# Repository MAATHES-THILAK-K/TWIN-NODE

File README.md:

## 📌 Project Overview

**TWIN-NODE** is a **two-node, ultra-low-power water level monitoring system** for overhead tanks.
It uses **ESP-NOW wireless communication**, requires **no internet**, and is optimized for **solar-powered outdoor operation**.

This project is **designed for manufacturable PCBs**, with all components chosen for reliability and low power.

---

## 🧩 System Architecture

| Node                             | Description                                                                             |
| -------------------------------- | --------------------------------------------------------------------------------------- |
| **NODE-1 (Outdoor Sensor Node)** | Measures water level using a waterproof ultrasonic sensor and transmits data wirelessly |
| **NODE-2 (Indoor Display Node)** | Receives water level data and alerts the user using LEDs and a buzzer                   |

---

## 🔧 NODE-1 – Outdoor Sensor Node

| Feature       | Description                               |
| ------------- | ----------------------------------------- |
| Controller    | ESP-12F (ESP8266)                              |
| Sensor        | SR04M / JSN-SR04T Waterproof Ultrasonic /HCSRO4|
| Power Source  | 18650 Li-ion Battery                      |
| Charging      | Solar Panel + TP4056                      |
| Regulation    | RT9080-3.3 V LDO                          |
| Communication | ESP-NOW                                   |
| Power Saving  | Deep Sleep + GPIO-controlled sensor power |
| Installation  | Weatherproof Enclosure                    |

---

## 🔋 Low-Power Design

| Technique                      | Purpose                           |
| ------------------------------ | --------------------------------- |
| Deep Sleep Mode                | Minimizes battery consumption     |
| GPIO-controlled Sensor Power   | Cuts sensor standby current       |
| LDO with low quiescent current | Efficient voltage regulation      |
| ESP-NOW                        | Low-energy wireless communication |

---

## 📂 Repository Structure

| Folder            | Purpose                                                |
| ----------------- | ------------------------------------------------------ |
| `TWIN NODE V1.0/` | Stable, tested hardware revision                       |
| `TWIN NODE V2.0/` | Updated hardware revision (new features, improvements) |
| `Gerber/`         | Manufacturing-ready files                              |
| `IMAGES/`         | PCB renders and photos                                 |
| `REPORT/`         | ERC, DRC, design checks                                |
| `3D MODELS/`      | Mechanical references                                  |
| `LICENSE`         | Open-source licensing information                      |
| `README.md`       | Project overview and documentation                     |

---

## 🚀 Engineering Note

* Designed for **low-power operation**
* **Solar and battery-friendly**
* **Manufacturable PCB**
* Versioned structure makes it easy to track revisions

---

### 👤 Author

**MAATHES-THILAK-K (KMT)**
Embedded Systems | PCB Design | Robotics

---

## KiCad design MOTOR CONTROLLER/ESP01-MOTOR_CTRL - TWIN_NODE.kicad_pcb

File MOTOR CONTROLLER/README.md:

# ⚙️ TWIN-NODE – Motor Controller
## Overview

The **TWIN-NODE Motor Controller** is a compact wireless motor control module designed to work with the TWIN-NODE water level monitoring system.
It enables **remote ON/OFF control of a water pump** using **ESP-NOW**, without internet connectivity.

---

---

## Key Features

* ESP-01 (ESP8266) based controller
* Wireless control using ESP-NOW
* Relay-based motor switching
* Electrical isolation between control and load
* Manufacturable PCB design

---

## Hardware Summary

| Item          | Description        |
| ------------- | ------------------ |
| MCU           | ESP-01 (ESP8266)   |
| Communication | ESP-NOW            |
| Motor Control | Relay   |
| PCB Files     | KiCad + Gerber     |
| Application   | Water pump control |

---

## Repository Contents

* Gerber files for manufacturing
* KiCad schematic & PCB
* 3D models and images
* Design reports (ERC/DRC)

---

## Author

**MAATHES-THILAK-K (KMT)**
Embedded Systems | PCB Design | Robotics

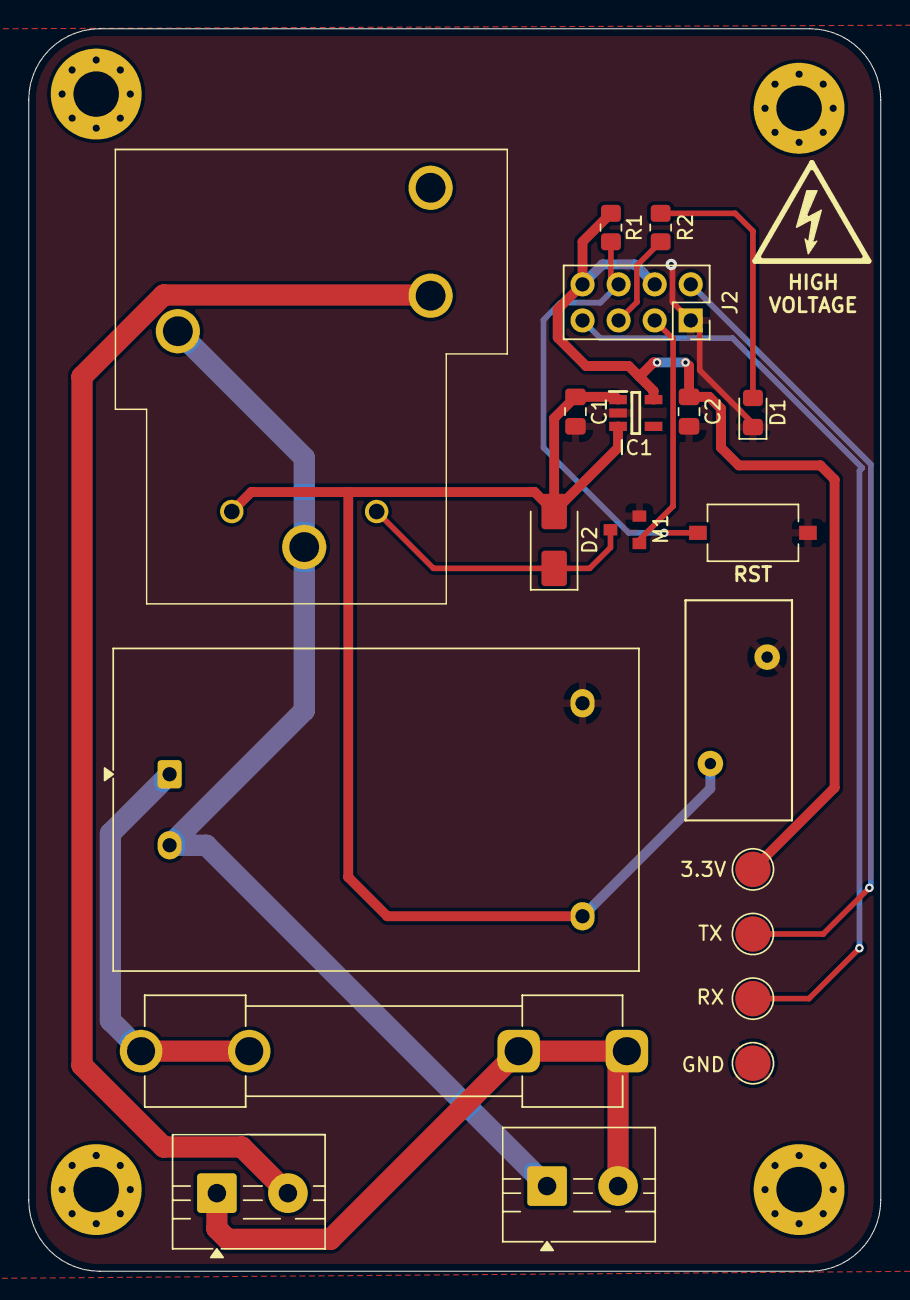
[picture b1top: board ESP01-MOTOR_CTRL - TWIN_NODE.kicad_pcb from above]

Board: 2 copper layers, 60.0 x 87.5 mm, 24 parts (0 on the bottom side), 14 nets.

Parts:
3.3V: TestPoint; TestPoint_Pad_D2.5mm
C1, C2: 10uF; C_0805_2012Metric_Pad1.18x1.45mm_HandSolder
D1: LED; LED_0805_2012Metric_Pad1.15x1.40mm_HandSolder
D2: SS12; D_SMA
F1: 250V@500mA; Fuseholder_Clip-6.3x32mm_Littelfuse_102_122_Inline_P34.21x7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
GND: TestPoint; TestPoint_Pad_D2.5mm
H1, H2, H3, H4: MH; MountingHole_3.2mm_M3_Pad_Via
IC1: RT9080-33GJ5; SOT94P280X100-5N
J1: MOTOR; TerminalBlock_MaiXu_MX126-5.0-02P_1x02_P5.00mm
J2: 02X04; PinSocket_2x04_P2.54mm_Vertical
J3: INPUT; TerminalBlock_MaiXu_MX126-5.0-02P_1x02_P5.00mm
K1: SLA-5VDC-SL-C; RELAY_SLA-12VDC-SL-C
M1: SI2300; SOT-23
PS1: HLK-PM01; Converter_ACDC_Hi-Link_HLK-PMxx
R1: 10K; R_0805_2012Metric_Pad1.20x1.40mm_HandSolder
R2: 1K; R_0805_2012Metric_Pad1.20x1.40mm_HandSolder
RV1: 275V-14D; RV_Disc_D15.5mm_W7.5mm_P7.5mm
RX: TestPoint; TestPoint_Pad_D2.5mm
SW1: SW_Push; SW_Tactile_SPST_NO_Straight_CK_PTS636Sx25SMTRLFS
TX: TestPoint; TestPoint_Pad_D2.5mm

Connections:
/3.3V: 3.3V.1, C2.1, IC1.5 (VOUT), J2.4, J2.8, R1.1
/5V: C1.1, D2.2 (A), IC1.1 (VIN), IC1.3 (EN), K1.C1, PS1.4 (+Vout), RV1.1
/RST: J2.6, R1.2, SW1.1
FUSED_LIVE: F1.2, PS1.1 (AC/L)
GND: C1.2, C2.2, D1.1 (K), GND.1, IC1.2 (GND), J2.1, M1.2, PS1.3 (-Vout), RV1.2, SW1.2
GPIO0: J2.5, R2.1
GPIO2: J2.3, M1.1
LIVE: F1.1, J1.1, J3.2
NEUTRAL: J3.1, K1.COM1, K1.COM2, PS1.2 (AC/N)
NEUTRAL_BREAK: J1.2, K1.NO
unnamed: D1.2 (A), R2.2
unnamed: D2.1 (K), K1.C2, M1.3
RX: J2.7, RX.1
TX: J2.2, TX.1

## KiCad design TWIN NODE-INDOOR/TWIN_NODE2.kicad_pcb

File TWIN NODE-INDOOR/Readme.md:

# TWIN-NODE – Indoor Node

## Overview

The **Indoor Node** is a **battery-powered, ultra-low-power receiver and alert unit** for the TWIN-NODE water level monitoring system.
It receives water level data from the outdoor sensor node using **ESP-NOW** and provides **local LED and buzzer alerts**, without internet or Wi-Fi infrastructure.

---

## Key Features

* ESP-NOW wireless communication
* Battery-powered operation
* Ultra-low-power design
* LED level indication
* Buzzer alert for critical levels
* No internet, no router, no cloud

---

## Hardware Summary

| Item          | Specification     |
| ------------- | ----------------- |
| MCU           | ESP-12F (ESP8266) |
| Communication | ESP-NOW           |
| Indicators    | LEDs              |
| Alert         | Buzzer            |
| Power Source  | Battery           |
| Design Tool   | KiCad             |

---

## Power Design

* Deep sleep enabled
* Wake on ESP-NOW receive
* Minimal standby current
* Optimized for long-term battery life

---

## Repository Contents

| Path                 | Description         |
| -------------------- | ------------------- |
| `GERBER/`            | Manufacturing files |
| `IMAGES/`            | PCB images          |
| `REPORT/`            | ERC / DRC           |
| `3D MODELS/`         | Mechanical models   |
| `TWIN_NODE2.kicad_*` | Schematic & PCB     |

---

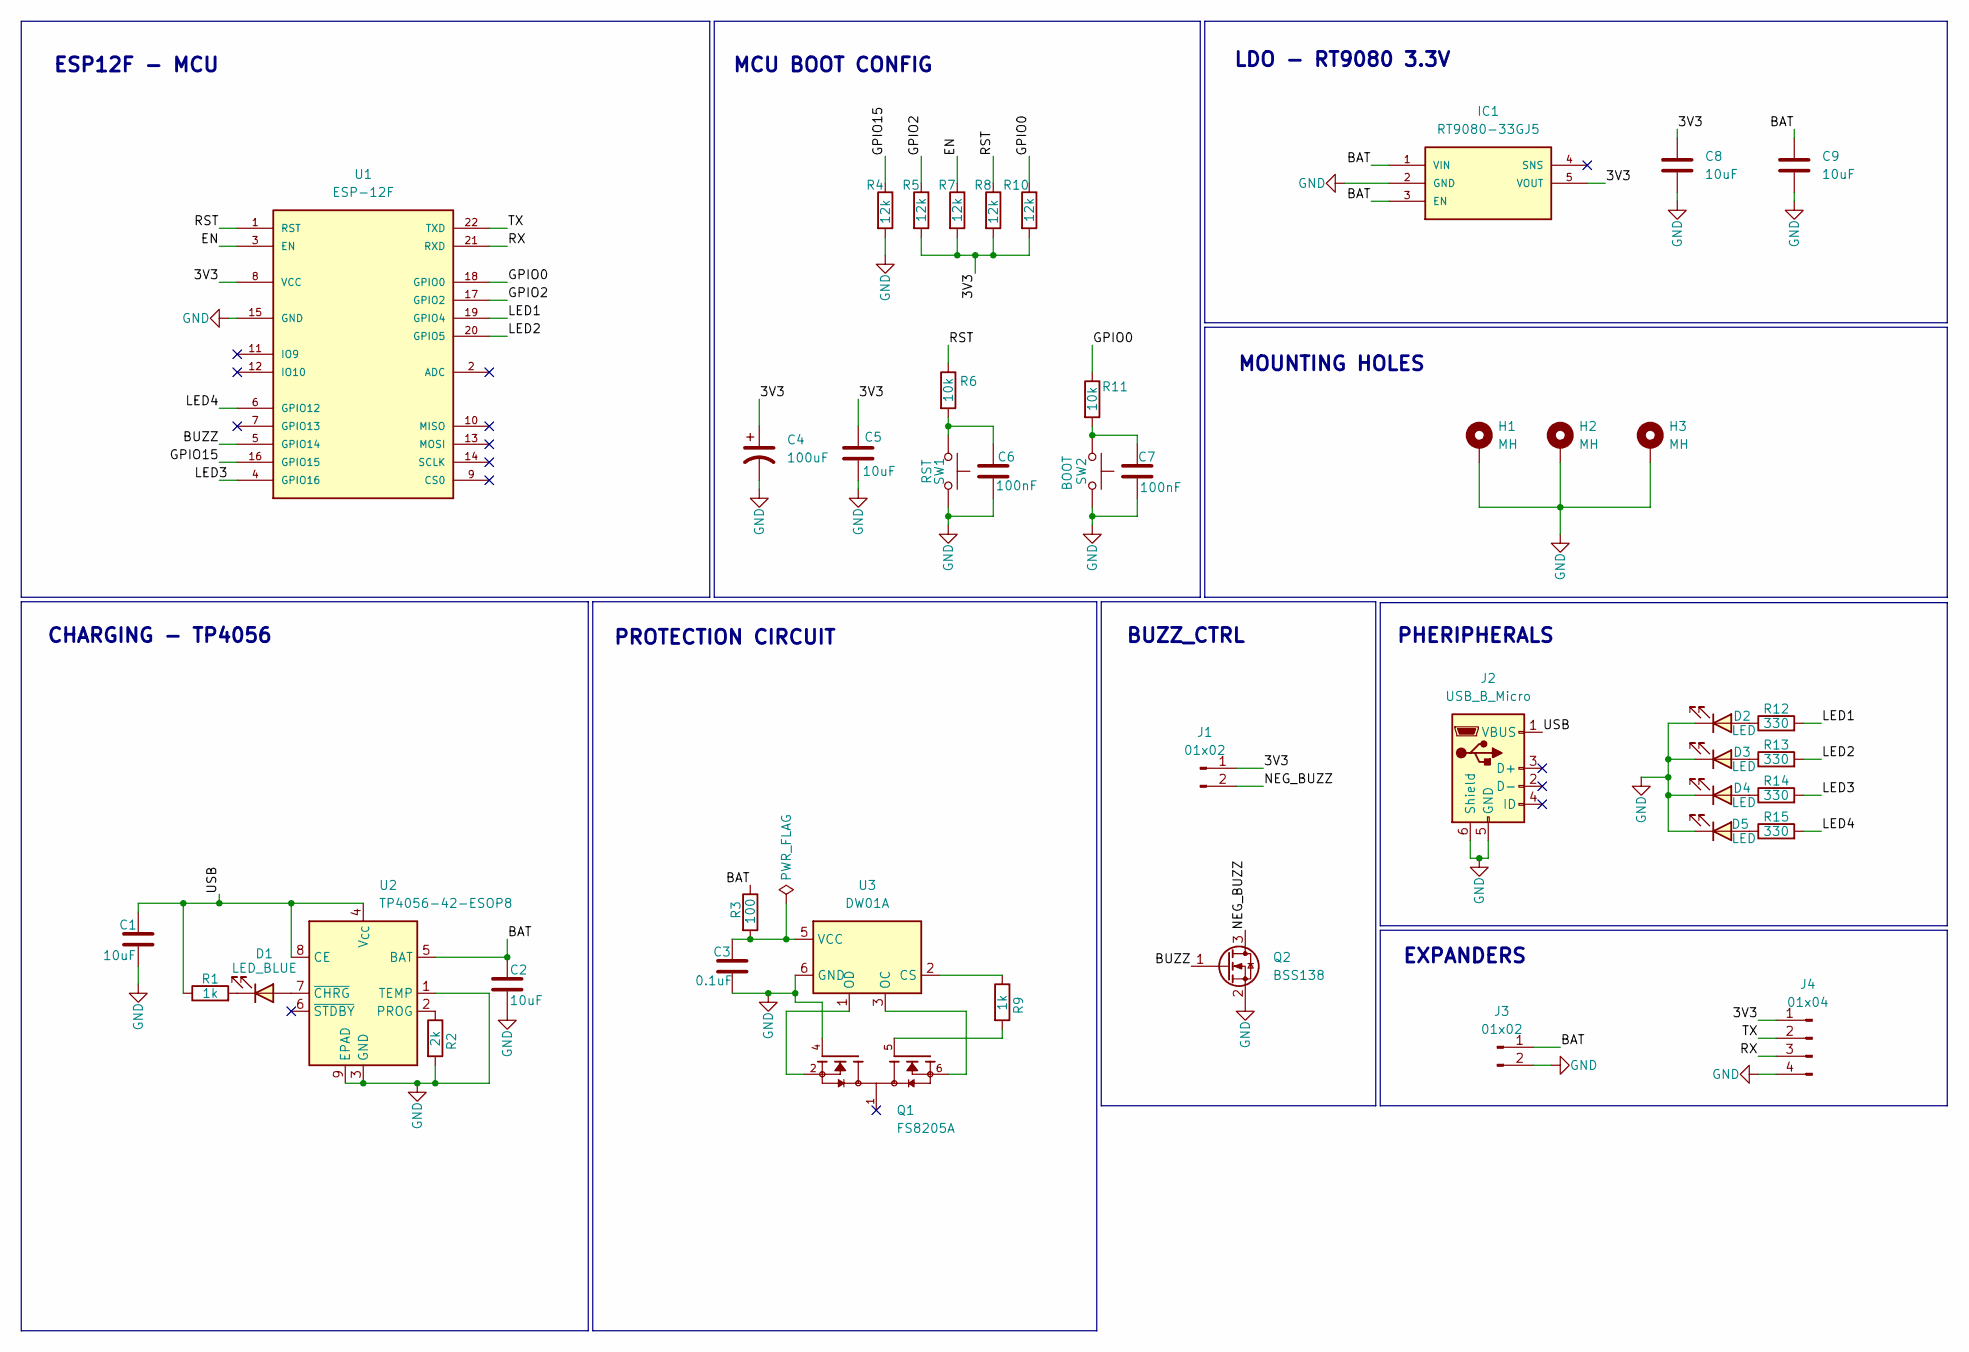
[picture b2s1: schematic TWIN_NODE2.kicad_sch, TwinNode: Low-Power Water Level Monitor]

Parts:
C1, C2, C5, C8, C9: 10uF; C_0805_2012Metric_Pad1.18x1.45mm_HandSolder
C3: 0.1uF; C_0805_2012Metric_Pad1.18x1.45mm_HandSolder
C4: 100uF; CP_Elec_5x5.3
C6, C7: 100nF; C_0805_2012Metric_Pad1.18x1.45mm_HandSolder
D1: LED_BLUE; SolderWire-0.1sqmm_1x02_P3.6mm_D0.4mm_OD1mm
D2, D3, D4, D5: LED; SolderWire-0.1sqmm_1x02_P3.6mm_D0.4mm_OD1mm
H1, H2, H3: MH; MountingHole_3.2mm_M3_Pad_Via
IC1: RT9080-33GJ5; SOT94P280X100-5N
J1: 01x02; SolderWire-0.1sqmm_1x02_P3.6mm_D0.4mm_OD1mm
J2: USB_B_Micro; USB_Micro-B_Molex_47346-0001
J3: 01x02; JST_SH_SM02B-SRSS-TB_1x02-1MP_P1.00mm_Horizontal
J4: 01x04; JST_SH_SM04B-SRSS-TB_1x04-1MP_P1.00mm_Horizontal
Q1: FS8205A; SOP65P640X120-8N; PARTREV 1.7
Q2: BSS138; SOT-23
R1, R9: 1k; R_0805_2012Metric_Pad1.20x1.40mm_HandSolder
R2: 2k; R_0805_2012Metric_Pad1.20x1.40mm_HandSolder
R3: 100; R_0805_2012Metric_Pad1.20x1.40mm_HandSolder
R4, R5, R7, R8, R10: 12k; R_0805_2012Metric_Pad1.20x1.40mm_HandSolder
R6, R11: 10k; R_0805_2012Metric_Pad1.20x1.40mm_HandSolder
R12, R13, R14, R15: 330; R_0805_2012Metric_Pad1.20x1.40mm_HandSolder
SW1: RST; SW_Tactile_SPST_NO_Straight_CK_PTS636Sx25SMTRLFS
SW2: BOOT; SW_Tactile_SPST_NO_Straight_CK_PTS636Sx25SMTRLFS
U1: ESP-12F
U2: TP4056-42-ESOP8; SOIC-8-1EP_3.9x4.9mm_P1.27mm_EP2.41x3.3mm_ThermalVias
U3: DW01A; SOT-23-6

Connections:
/3V3: C4.1, C5.1, C8.1, IC1.5 (VOUT), J1.1, J4.1, R5.2, R7.2, R8.2, R10.2, U1.8 (VCC)
/BAT: C2.1, C9.1, IC1.1 (VIN), IC1.3 (EN), J3.1, R3.1, U2.5 (BAT)
/BUZZ: Q2.1 (G), U1.5 (GPIO14)
/EN: R7.1, U1.3 (EN)
/GPIO0: R10.1, R11.1, U1.18 (GPIO0)
/GPIO2: R5.1, U1.17 (GPIO2)
/GPIO15: R4.1, U1.16 (GPIO15)
/LED1: R12.2, U1.19 (GPIO4)
/LED2: R13.2, U1.20 (GPIO5)
/LED3: R14.2, U1.4 (GPIO16)
/LED4: R15.2, U1.6 (GPIO12)
/NEG_BUZZ: J1.2, Q2.3 (D)
/RST: R6.1, R8.1, U1.1 (RST)
/RX: J4.3, U1.21 (RXD)
/TX: J4.2, U1.22 (TXD)
/USB: C1.1, J2.1 (VBUS), R1.1, U2.4 (V_{CC}), U2.8 (CE)
GND: C1.2, C2.2, C3.2, C4.2, C5.2, C6.2, C7.2, C8.2, C9.2, D2.1 (K), D3.1 (K), D4.1 (K), D5.1 (K), H1.1, H2.1, H3.1, IC1.2 (GND), J2.5 (GND), J2.6 (Shield), J3.2, J4.4, Q1.4, Q2.2 (S), R2.2, R4.2, SW1.2, SW2.2, U1.15 (GND), U2.1 (TEMP), U2.3 (GND), U2.9 (EPAD), U3.6 (GND)
unnamed: C6.1, R6.2, SW1.1
unnamed: C7.1, R11.2, SW2.1
unnamed: D1.2 (A), U2.7 (~CHRG)
unnamed: D1.1 (K), R1.2
unnamed: D2.2 (A), R12.1
unnamed: D3.2 (A), R13.1
unnamed: D4.2 (A), R14.1
unnamed: D5.2 (A), R15.1
unnamed: Q1.5, R9.2
unnamed: R2.1, U2.2 (PROG)
unnamed: R9.1, U3.2 (CS)
unnamed: Q1.6, Q1.7, U3.3 (OC)
unnamed: Q1.2, Q1.3, U3.1 (OD)
unnamed: C3.1, R3.2, U3.5 (VCC)

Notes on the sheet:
MCU BOOT CONFIG
CHARGING - TP4056
EXPANDERS
ESP12F - MCU
LDO - RT9080 3.3V
PROTECTION CIRCUIT
BUZZ_CTRL
MOUNTING HOLES
PHERIPHERALS

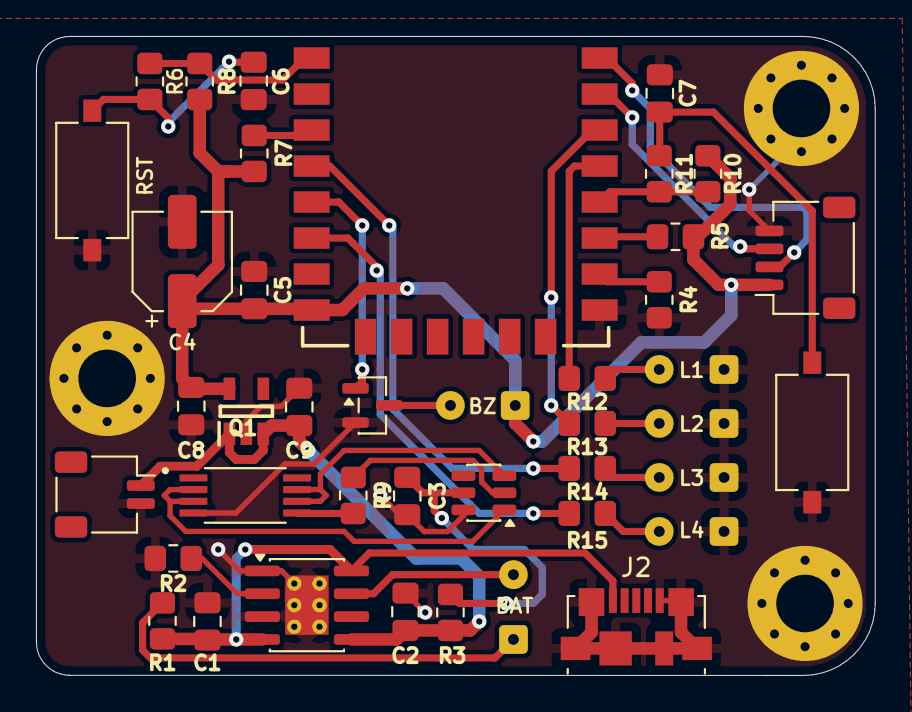
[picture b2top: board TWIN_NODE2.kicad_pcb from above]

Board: 2 copper layers, 46.6 x 35.5 mm, 44 parts (0 on the bottom side), 31 nets.

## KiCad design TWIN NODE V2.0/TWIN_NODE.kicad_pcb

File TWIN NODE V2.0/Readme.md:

# TWIN NODE V2.0

### Low-Power Outdoor Water Level Sensor Node – Improved Design

---

## 📌 Overview

**TWIN NODE V2.0** is the **fabricated and tested hardware revision** of the low-power ESP-NOW water level monitoring system.
This version incorporates **real-world fabrication feedback**, improving reliability and simplifying the design for future revisions.

All components are sourced from [ROBU.IN](https://robu.in).

---

## ⚙️ Key Updates from V1.0

* **Mounting holes:** Increased from 3 to **4** for better casing support
* **I2C expanders:** Removed, no longer required
* **Programming & power connections:** Female headers replaced with **JST connectors**
* **Component placement:** Fully optimized for **aesthetic and practical routing**
* **PCB traces:** Increased width to support **longer interconnections**
* **PCB size:** ~45 × 45 mm
* **DRC & ERC:** Fully verified
* **Fabricated & powered ON successfully**

---

## 🛠️ Fabrication Feedback & Design Correction (Important)

During physical testing of the fabricated PCB, the following observation was made:

### ❌ Unnecessary Pull-Up Resistors Identified

* **GPIO0 (BOOT)** – 10 kΩ resistor **not required**
* **RST (RESET)** – 10 kΩ resistor **not required**

These resistors were found to be **redundant** and **can be safely removed** in future PCB revisions.

### ✅ Reason

* ESP8266 12K pull-ups are sufficient for:

  * Normal boot operation
  * Reliable reset behavior
* External 10 kΩ resistors on **GPIO0** and **RST**:

  * Do **not improve stability**
  * Increase component count unnecessarily
  * Slightly complicate routing and assembly

➡️ **Action for next revision:**
Remove the 10 kΩ pull-up resistors on **GPIO0 (BOOT)** and **RST**.

---

## 🔧 Design Notes

* Designed for **battery + solar operation**
* Optimized for **low power outdoor deployment**
* ESP-NOW based communication (no Wi-Fi AP dependency)
* Layout finalized with **manufacturability in mind**
* Suitable for **field deployment and enclosure mounting**

---

## 📦 Project Status

✔ PCB fabricated
✔ Power-up verified
✔ Boot & reset behavior validated
✔ Design improvement identified for next revision

---

### 👤 Author

**MAATHES-THILAK-K (KMT)**
Embedded Systems | PCB Design | Robotics

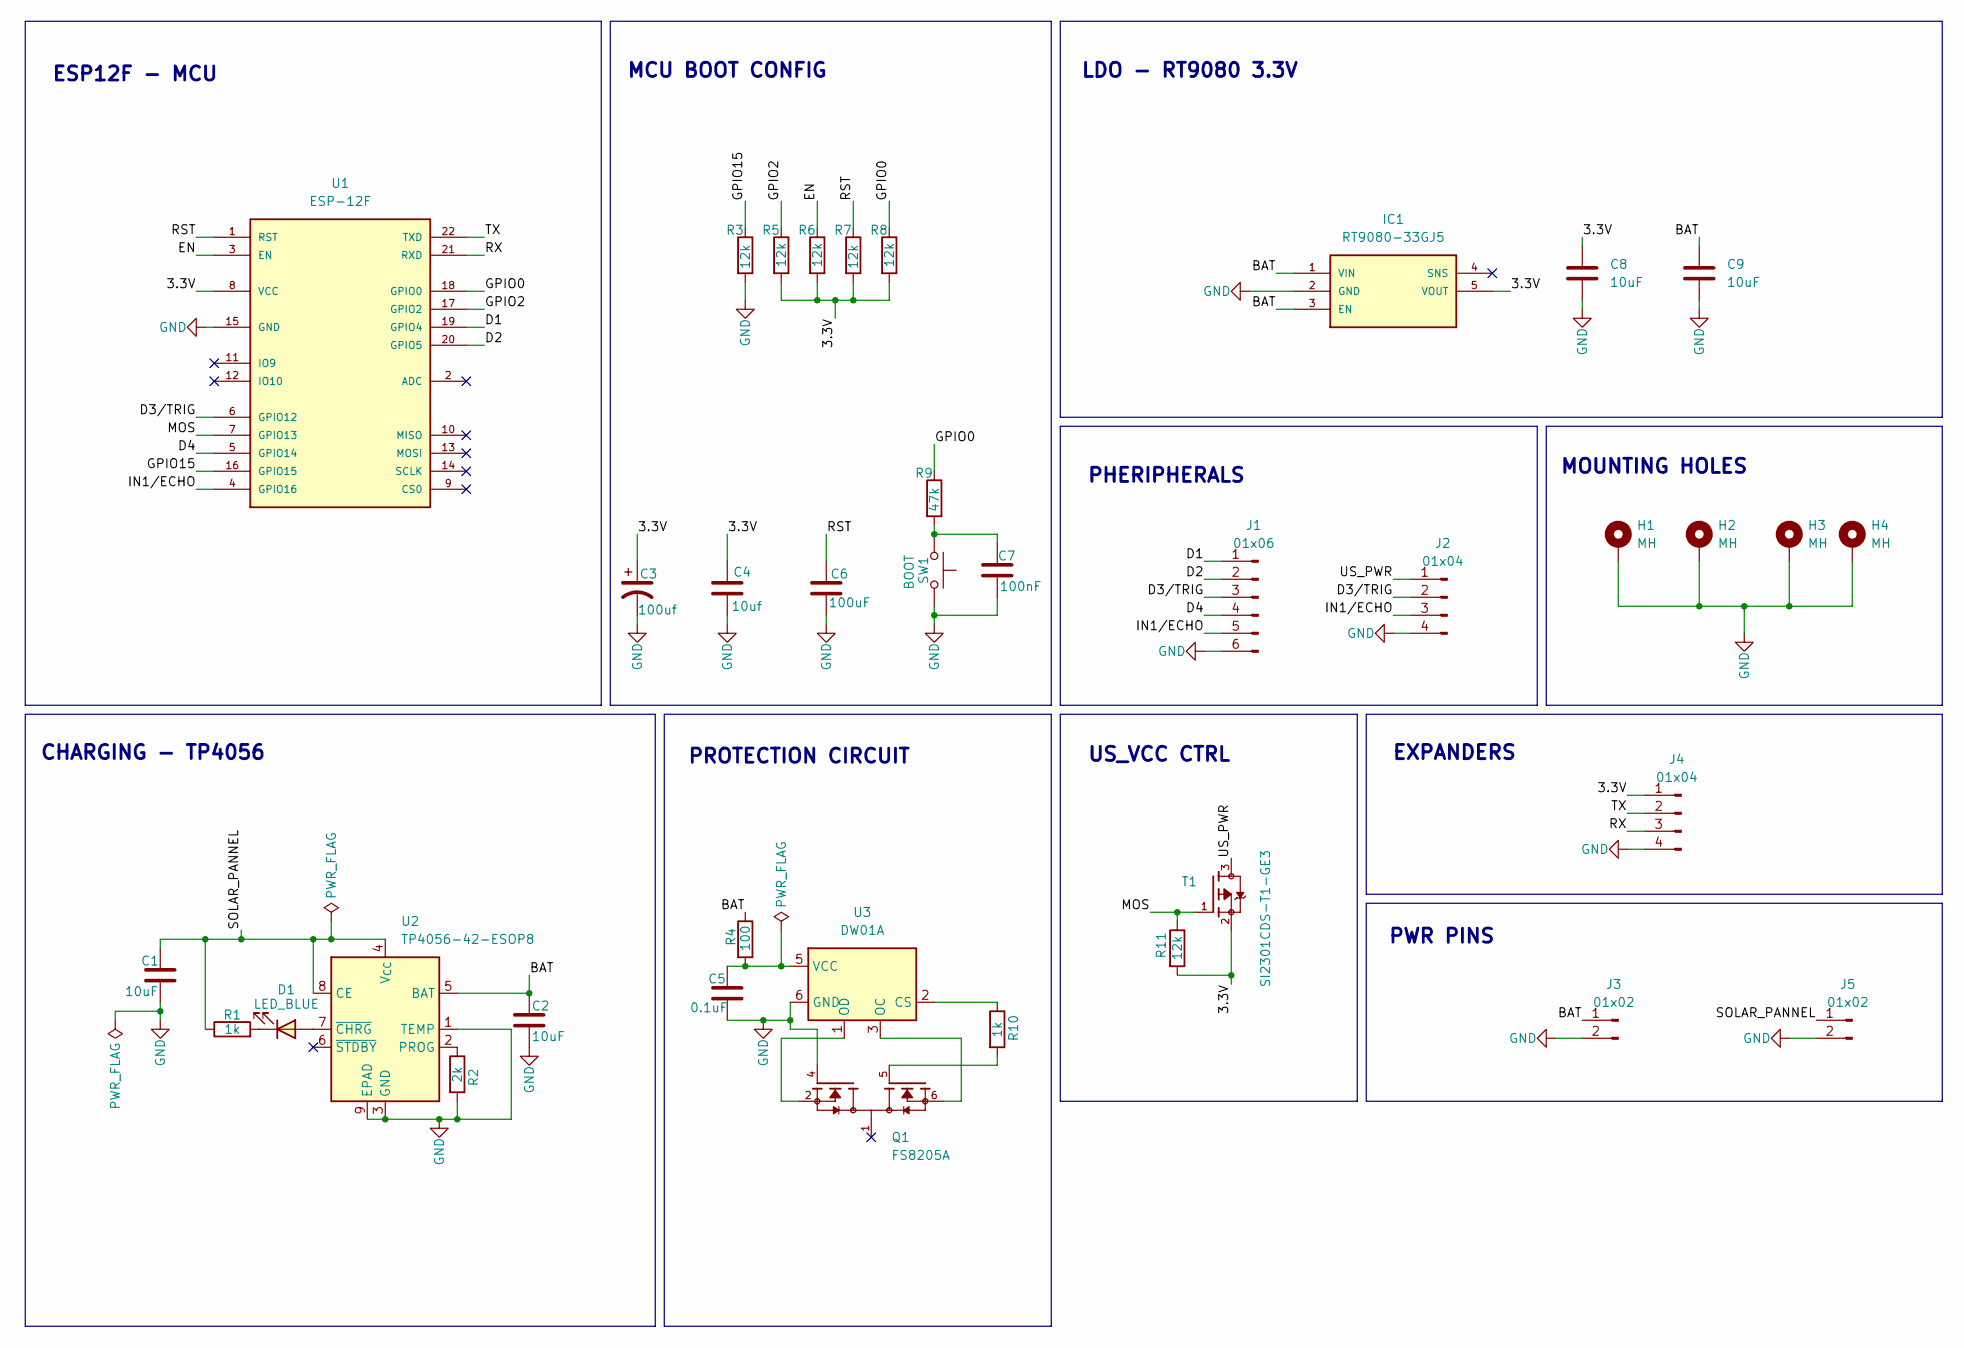
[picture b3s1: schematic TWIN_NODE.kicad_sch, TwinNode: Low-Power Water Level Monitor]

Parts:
C1, C2, C8, C9: 10uF; C_0805_2012Metric_Pad1.18x1.45mm_HandSolder
C3: 100uf; CP_Elec_8x10.5
C4: 10uf; C_0805_2012Metric_Pad1.18x1.45mm_HandSolder
C5: 0.1uF; C_0805_2012Metric_Pad1.18x1.45mm_HandSolder
C6: 100uF; C_0805_2012Metric_Pad1.18x1.45mm_HandSolder
C7: 100nF; C_0805_2012Metric_Pad1.18x1.45mm_HandSolder
D1: LED_BLUE; LED_0805_2012Metric_Pad1.15x1.40mm_HandSolder
H1, H2, H3, H4: MH; MountingHole_3.2mm_M3_Pad_Via
IC1: RT9080-33GJ5; SOT94P280X100-5N
J1: 01x06; JST_SH_SM06B-SRSS-TB_1x06-1MP_P1.00mm_Horizontal
J2, J4: 01x04; JST_SH_SM04B-SRSS-TB_1x04-1MP_P1.00mm_Horizontal
J3, J5: 01x02; JST_SH_SM02B-SRSS-TB_1x02-1MP_P1.00mm_Horizontal
Q1: FS8205A; SOP65P640X120-8N; PARTREV 1.7
R1, R10: 1k; R_0805_2012Metric_Pad1.20x1.40mm_HandSolder
R2: 2k; R_0805_2012Metric_Pad1.20x1.40mm_HandSolder
R3, R5, R6, R7, R8, R11: 12k; R_0805_2012Metric_Pad1.20x1.40mm_HandSolder
R4: 100; R_0805_2012Metric_Pad1.20x1.40mm_HandSolder
R9: 47k; R_0805_2012Metric_Pad1.20x1.40mm_HandSolder
SW1: BOOT; SW_Tactile_SPST_NO_Straight_CK_PTS636Sx25SMTRLFS
T1: SI2301CDS-T1-GE3; SOT-23
U1: ESP-12F
U2: TP4056-42-ESOP8; SOIC-8-1EP_3.9x4.9mm_P1.27mm_EP2.41x3.3mm_ThermalVias
U3: DW01A; SOT-23-6

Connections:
/3.3V: C3.1, C4.1, C8.1, IC1.5 (VOUT), J4.1, R5.2, R6.2, R7.2, R8.2, R11.2, T1.2, U1.8 (VCC)
/BAT: C2.1, C9.1, IC1.1 (VIN), IC1.3 (EN), J3.1, R4.1, U2.5 (BAT)
/D1: J1.1, U1.19 (GPIO4)
/D2: J1.2, U1.20 (GPIO5)
/D3/TRIG: J1.3, J2.2, U1.6 (GPIO12)
/D4: J1.4, U1.5 (GPIO14)
/EN: R6.1, U1.3 (EN)
/GPIO0: R8.1, R9.1, U1.18 (GPIO0)
/GPIO2: R5.1, U1.17 (GPIO2)
/GPIO15: R3.1, U1.16 (GPIO15)
/IN1/ECHO: J1.5, J2.3, U1.4 (GPIO16)
/MOS: R11.1, T1.1, U1.7 (GPIO13)
/RST: C6.1, R7.1, U1.1 (RST)
/RX: J4.3, U1.21 (RXD)
/SOLAR_PANNEL: C1.1, J5.1, R1.1, U2.4 (V_{CC}), U2.8 (CE)
/TX: J4.2, U1.22 (TXD)
/US_PWR: J2.1, T1.3
GND: C1.2, C2.2, C3.2, C4.2, C5.2, C6.2, C7.2, C8.2, C9.2, H1.1, H2.1, H3.1, H4.1, IC1.2 (GND), J1.6, J2.4, J3.2, J4.4, J5.2, Q1.4, R2.2, R3.2, SW1.2, U1.15 (GND), U2.1 (TEMP), U2.3 (GND), U2.9 (EPAD), U3.6 (GND)
unnamed: C7.1, R9.2, SW1.1
unnamed: D1.2 (A), U2.7 (~CHRG)
unnamed: D1.1 (K), R1.2
unnamed: Q1.5, R10.2
unnamed: R2.1, U2.2 (PROG)
unnamed: R10.1, U3.2 (CS)
unnamed: Q1.6, Q1.7, U3.3 (OC)
unnamed: Q1.2, Q1.3, U3.1 (OD)
unnamed: C5.1, R4.2, U3.5 (VCC)

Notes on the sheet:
MCU BOOT CONFIG
LDO - RT9080 3.3V
US_VCC CTRL
ESP12F - MCU
PWR PINS
CHARGING - TP4056
PHERIPHERALS
EXPANDERS
MOUNTING HOLES
PROTECTION CIRCUIT

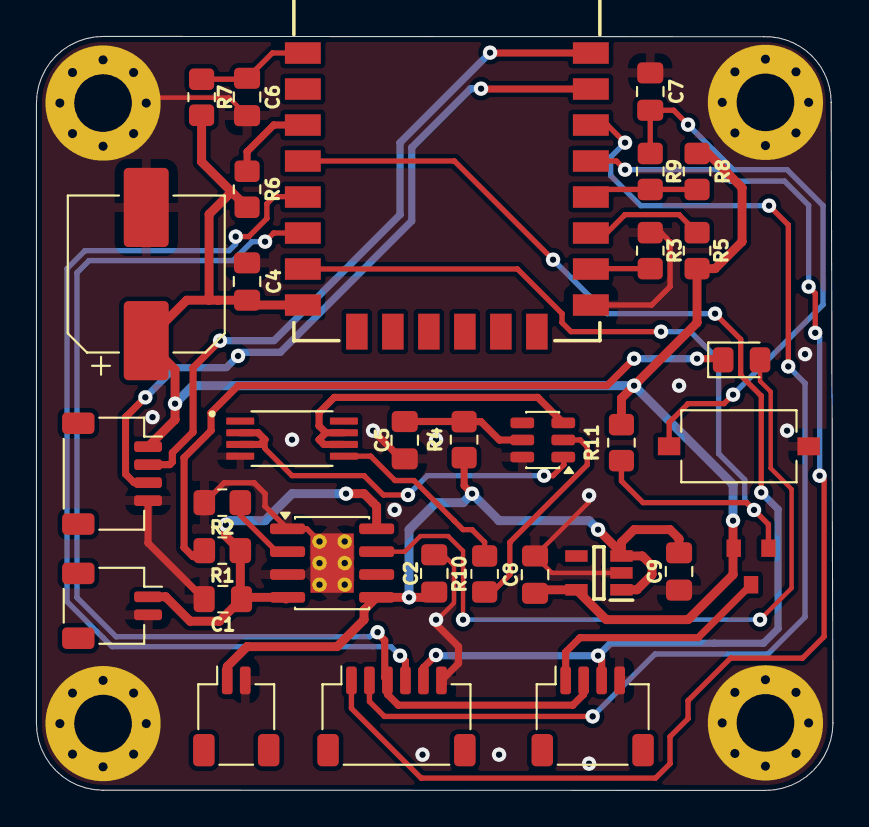
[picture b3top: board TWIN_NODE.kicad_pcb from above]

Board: 2 copper layers, 44.2 x 41.9 mm, 37 parts (0 on the bottom side), 27 nets.

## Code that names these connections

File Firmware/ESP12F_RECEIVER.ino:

#include <Arduino.h>
#include <ESP8266WiFi.h>
#include <espnow.h>

extern "C" {
  #include <user_interface.h>
}
//ESP12F MAC Address: 24:4C:AB:6C:E4:F8 - LION PCB TRANSMITTER
// --------------------------------------------------
// ESP32 TRANSMITTER MAC ADDRESS
// TX MAC Address: 24:6F:28:3A:B5:68
// --------------------------------------------------
uint8_t transmitterMacAddress[] = {0x24, 0x4C, 0xAB, 0x6C, 0xE4, 0xF8};

// --------------------------------------------------
// PIN CONFIGURATION - ESP12F RECEIVER
// --------------------------------------------------
#define LED_LOW_PIN     12   // GPIO12 - LOW level LED
#define LED_MED_PIN     16   // GPIO16 - MEDIUM level LED
#define LED_HIGH_PIN    5    // GPIO5  - HIGH level LED
#define LED_FULL_PIN    4    // GPIO4  - FULL level LED

#define BUZZER_PIN      14   // GPIO14 - Buzzer

// --------------------------------------------------
// ESP-NOW CHANNEL
// Must match transmitter channel
// --------------------------------------------------
#define ESPNOW_CHANNEL  1

// --------------------------------------------------
// DATA STRUCTURE
// Must match ESP32 transmitter structure
// --------------------------------------------------
typedef struct struct_message {
  float distanceCm;
  int waterPercent;
  int level;
  bool tankFull;
  bool tankEmpty;
} struct_message;

struct_message receivedData;

// --------------------------------------------------
// PRINT MAC ADDRESS
// --------------------------------------------------
void printMacAddress(uint8_t *mac) {
  for (int i = 0; i < 6; i++) {
    if (mac[i] < 16) Serial.print("0");
    Serial.print(mac[i], HEX);
    if (i < 5) Serial.print(":");
  }
}

// --------------------------------------------------
// CHECK KNOWN TRANSMITTER
// --------------------------------------------------
bool isFromKnownTransmitter(uint8_t *mac) {
  for (int i = 0; i < 6; i++) {
    if (mac[i] != transmitterMacAddress[i]) {
      return false;
    }
  }
  return true;
}

// --------------------------------------------------
// TURN OFF ALL LEDS
// --------------------------------------------------
void allLedsOff() {
  digitalWrite(LED_LOW_PIN, LOW);
  digitalWrite(LED_MED_PIN, LOW);
  digitalWrite(LED_HIGH_PIN, LOW);
  digitalWrite(LED_FULL_PIN, LOW);
}

// --------------------------------------------------
// UPDATE 4 LEVEL LED STATUS
// --------------------------------------------------
void updateLevelLEDs(int waterPercent) {
  allLedsOff();

  if (waterPercent < 0) {
    Serial.println("Invalid water percentage. LEDs OFF.");
    return;
  }

  if (waterPercent <= 25) {
    digitalWrite(LED_LOW_PIN, HIGH);
    Serial.println("LED Status: LOW");
  }
  else if (waterPercent <= 50) {
    digitalWrite(LED_MED_PIN, HIGH);
    Serial.println("LED Status: MEDIUM");
  }
  else if (waterPercent <= 80) {
    digitalWrite(LED_HIGH_PIN, HIGH);
    Serial.println("LED Status: HIGH");
  }
  else {
    digitalWrite(LED_FULL_PIN, HIGH);
    Serial.println("LED Status: FULL");
  }
}

// --------------------------------------------------
// BUZZER ONLY DURING FULL LEVEL
// --------------------------------------------------
void updateBuzzer(int waterPercent) {
  if (waterPercent > 80) {
    Serial.println("BUZZER: FULL alert");

    digitalWrite(BUZZER_PIN, HIGH);
    delay(1000);
    digitalWrite(BUZZER_PIN, LOW);
  }
  else {
    digitalWrite(BUZZER_PIN, LOW);
  }
}

// --------------------------------------------------
// ESP-NOW RECEIVE CALLBACK - ESP8266 FORMAT
// --------------------------------------------------
void onDataReceived(uint8_t *mac, uint8_t *incomingData, uint8_t len) {
  Serial.println();
  Serial.println("Data Received!");

  Serial.print("Sender MAC: ");
  printMacAddress(mac);
  Serial.println();

  if (!isFromKnownTransmitter(mac)) {
    Serial.println("Unknown transmitter. Data ignored.");
    return;
  }

  if (len != sizeof(receivedData)) {
    Serial.println("Data size mismatch!");
    Serial.print("Received size: ");
    Serial.println(len);
    Serial.print("Expected size: ");
    Serial.println(sizeof(receivedData));
    return;
  }

  memcpy(&receivedData, incomingData, sizeof(receivedData));

  Serial.println("------ Tank Data ------");

  Serial.print("Distance: ");
  Serial.print(receivedData.distanceCm);
  Serial.println(" cm");

  Serial.print("Water Percentage: ");
  Serial.print(receivedData.waterPercent);
  Serial.println(" %");

  Serial.print("Received Level: ");
  Serial.println(receivedData.level);

  Serial.print("Tank Full: ");
  Serial.println(receivedData.tankFull ? "YES" : "NO");

  Serial.print("Tank Empty: ");
  Serial.println(receivedData.tankEmpty ? "YES" : "NO");

  Serial.println("-----------------------");

  updateLevelLEDs(receivedData.waterPercent);
  updateBuzzer(receivedData.waterPercent);
}

// --------------------------------------------------
// SETUP
// --------------------------------------------------
void setup() {
  Serial.begin(115200);
  delay(1000);

  Serial.println();
  Serial.println("ESP12F Indoor Receiver Node Started");

  pinMode(LED_LOW_PIN, OUTPUT);
  pinMode(LED_MED_PIN, OUTPUT);
  pinMode(LED_HIGH_PIN, OUTPUT);
  pinMode(LED_FULL_PIN, OUTPUT);
  pinMode(BUZZER_PIN, OUTPUT);

  allLedsOff();
  digitalWrite(BUZZER_PIN, LOW);

  WiFi.mode(WIFI_STA);
  WiFi.disconnect();

  wifi_set_channel(ESPNOW_CHANNEL);

  Serial.print("Receiver ESP12F MAC Address: ");
  Serial.println(WiFi.macAddress());

  Serial.print("Expected Transmitter MAC: ");
  printMacAddress(transmitterMacAddress);
  Serial.println();

  Serial.print("Receiver Struct Size: ");
  Serial.println(sizeof(receivedData));

  if (esp_now_init() != 0) {
    Serial.println("ESP-NOW Init Failed!");
    return;
  }

  esp_now_set_self_role(ESP_NOW_ROLE_SLAVE);
  esp_now_register_recv_cb(onDataReceived);

  Serial.println("ESP-NOW Receiver Ready...");
}

// --------------------------------------------------
// LOOP
// --------------------------------------------------
void loop() {
  // Nothing needed here.
  // Data is handled inside onDataReceived().
}

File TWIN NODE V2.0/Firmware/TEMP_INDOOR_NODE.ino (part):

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// --- LED Level Bands (%) ---
//   LED1 lights when level ≥ LED1_THRESHOLD
//   LED2 lights when level ≥ LED2_THRESHOLD  … and so on
#define LED1_THRESHOLD        5       // 0–25% band  (show LED1 even at very low level)
#define LED2_THRESHOLD        25      // 25–50% band
#define LED3_THRESHOLD        50      // 50–75% band
#define LED4_THRESHOLD        75      // 75–100% band
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//  📌  PIN DEFINITIONS  — Adjust for your wiring
// ============================================================

#define LED1_PIN      D1    // GPIO 5  — Level 0–25%
#define LED2_PIN      D2    // GPIO 4  — Level 25–50%
#define LED3_PIN      D5    // GPIO 14 — Level 50–75%
#define LED4_PIN      D6    // GPIO 12 — Level 75–100%
#define BUZZER_PIN    D7    // GPIO 13 — Active buzzer

// ============================================================
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// ============================================================

void updateLEDs(uint8_t levelPct) {
  digitalWrite(LED1_PIN, (levelPct >= LED1_THRESHOLD) ? HIGH : LOW);
  digitalWrite(LED2_PIN, (levelPct >= LED2_THRESHOLD) ? HIGH : LOW);
  digitalWrite(LED3_PIN, (levelPct >= LED3_THRESHOLD) ? HIGH : LOW);
  digitalWrite(LED4_PIN, (levelPct >= LED4_THRESHOLD) ? HIGH : LOW);
}

void allLEDsOff() {
  digitalWrite(LED1_PIN, LOW);
  digitalWrite(LED2_PIN, LOW);
  digitalWrite(LED3_PIN, LOW);
  digitalWrite(LED4_PIN, LOW);
}

void allLEDsOn() {
  digitalWrite(LED1_PIN, HIGH);
  digitalWrite(LED2_PIN, HIGH);
  digitalWrite(LED3_PIN, HIGH);
  digitalWrite(LED4_PIN, HIGH);
}

// Blink all LEDs together — used for startup animation & warnings
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// Cascade blink (LED1 → LED4 → LED1) — startup flair
void cascadeLEDs(int sweeps, int stepMs) {
  for (int s = 0; s < sweeps; s++) {
    uint8_t pins[4] = { LED1_PIN, LED2_PIN, LED3_PIN, LED4_PIN };
    // Up sweep
    for (int i = 0; i < 4; i++) {
      allLEDsOff();
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  Serial.println("╚══════════════════════════════════════════╝");

  // ── GPIO Init ───────────────────────────────────────────
  pinMode(LED1_PIN,   OUTPUT);
  pinMode(LED2_PIN,   OUTPUT);
  pinMode(LED3_PIN,   OUTPUT);
  pinMode(LED4_PIN,   OUTPUT);
  pinMode(BUZZER_PIN, OUTPUT);

  allLEDsOff();
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
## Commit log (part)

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2026-01-04 Add TWIN NODE V1.0 project files
2026-01-04 Reorganize project files into TWIN NODE V1.0 folder
2026-01-04 Add TWIN NODE V2.0 hardware design files
2026-01-04 Remove TWIN NODE V2.0 files
2026-01-04 Remove TWIN NODE V1.0 files
2026-01-04 Create TEMP
2026-01-04 Create LICENSE
2026-01-23 Create TWIN_NODE-INDOOR
2026-01-25 Create 3D MODEL
2026-02-15 Remove empty line in Readme.md
2026-03-21 Its AI generated based on the Custom ALGORITHM
    The Final Firmware will be released Soon !!
